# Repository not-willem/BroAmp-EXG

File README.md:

# BroAmp EXG
a decent sized bio amp so i can wire it myself and so that it will be cheaper to produce unlike the other ones on the market 

go to the website i made [here](https://not-willem.github.io/BroAmp-EXG/)

# overview
BroAmp EXG is an open-source project created by yours truly that allows you to turn different body functions that produce a small amount of electricity and amplify them into a more readable signal.

## features 
 - same as the BioAmp EXG Pill just easier to produce using cheap parts
 - can do EEG (activity in parts of the brain), EMG (muscle activity, e.g when you move your hand), ECG (heart rate detection) and EOG (eye blink detection)
 - i think you could probably use it for more but thats all that it was listed for on the original page
 - it can send the data back to pretty much any microcontroller with an analog input (ADC)
 - you can configure the gain, bandpass, filter and electrodes all on the board itself

## documentation 
 - original project: [here](https://github.com/upsidedownlabs/BioAmp-EXG-Pill)
 - date of modifications: June 2026
 - i have made the capacitors and resistors larger to make it easier to hand solder/machine
 - i have changed the board dimensions to 36.5 mm x 48 mm to again, make it easier to hand solder/machine
 - i have kept the same licsense on the hardware (CERN OHL S v2)
 - i have acknowledged the source on the silkscreen
 - the complete source for the modified design is in this github that you're reading this from

## using the project files
To use the project files provided, download them using the green "Code" button at the top of the page, then Download Zip. All the PCB production files are kept in the "production" folder apart from the BOM.csv which is kept in the main folder. 

## production notes
the only thing you should need to do more micro-soldering for is the main chip itself and the electrodes and bandpass filters. these are optional and you will need to micro solder that on but they are for configuration, which, to be fair you could probably also do on the microcontroller itself. The components can simply be hand soldered and they are spaced apart well enough to not short out in case the wires are touching if you've gotten a bigger capacitor/resistor

thanks to the project by [upsidedownlabs](https://github.com/upsidedownlabs/BioAmp-EXG-Pill) because it was super good and cool. 

software demos [here](https://github.com/upsidedownlabs/BioAmp-EXG-Pill#software)

you can find the pcb files in the production folder

and [here](https://github.com/not-willem/BroAmp-EXG/blob/main/BOM%20and%20notes.csv) some notes and a BOM that you can put straight into LCSC to get the parts

but yeah heres some photos

oh hello there

Also some wiring stuff

also theres more ways you can use this [here](https://github.com/upsidedownlabs/BioAmp-EXG-Pill/tree/main/graphics/circuits/v1.0), its the same pins to wire they're not called anything different.

I haven't actually built it YET (i'll update this when i do) but i've 3d printed a prototype so you can see the size of it

*stalagmite for scale

okay i think i need a hot plate for soldering the smd part but i cant get funded for it so i'll find alternative ways to do it

alright you can just use a heat gun awesome

ALSO big news everyone the total cost of parts per board comes in at around $12.17 NZD so hooray!

that's quite cheap compared to the $59.61 NZD for ONE from the actual website (btw you HAVE to buy 2 you can't just get one)

P.S reading it again it seems the kit i'm refering to comes with "Two BioAmp EXG Pill boards, 15 gel electrodes, four 3-pin angled pin headers, four 3-pin straight pin headers, six alligator clips, and two 1.5 mm electrode cables" but still I find it a little silly you can't just buy the boards themselves

Anyway I really hope you like this project and consider supporting me by starring this project and if you think you'd want to change anything you can fork the project then make a pull request

##### This design is released under the CERN Open Hardware Licence Version 2 - Strongly Reciprocal (CERN-OHL-S-2.0).

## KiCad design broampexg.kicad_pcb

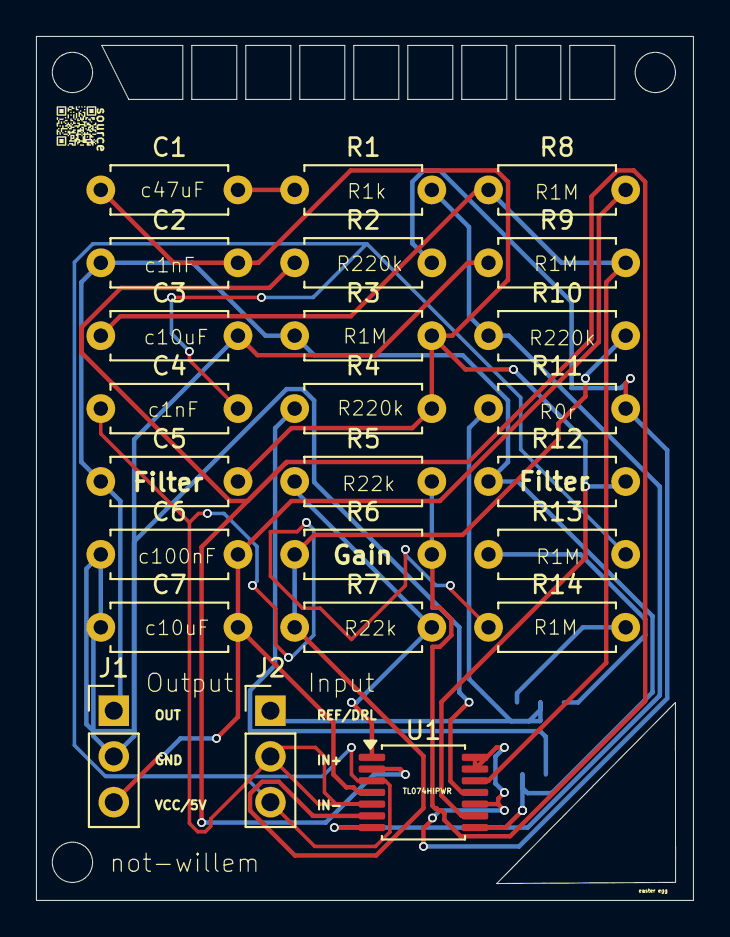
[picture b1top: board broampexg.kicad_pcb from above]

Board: 2 copper layers, 36.5 x 48.0 mm, 24 parts (0 on the bottom side), 14 nets.

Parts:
C1: 47uF; R_Axial_DIN0207_L6.3mm_D2.5mm_P7.62mm_Horizontal
C2, C4: 1nF; R_Axial_DIN0207_L6.3mm_D2.5mm_P7.62mm_Horizontal
C3, C7: 10uF; R_Axial_DIN0207_L6.3mm_D2.5mm_P7.62mm_Horizontal
C5: BPFC_C; R_Axial_DIN0207_L6.3mm_D2.5mm_P7.62mm_Horizontal
C6: 100nF; R_Axial_DIN0207_L6.3mm_D2.5mm_P7.62mm_Horizontal
J1: BioAmp Output; PinHeader_1x03_P2.54mm_Vertical
J2: BioAmp Input; PinHeader_1x03_P2.54mm_Vertical
R1: 1K; R_Axial_DIN0207_L6.3mm_D2.5mm_P7.62mm_Horizontal
R2, R4, R10: 220K; R_Axial_DIN0207_L6.3mm_D2.5mm_P7.62mm_Horizontal
R3, R8, R9, R13, R14: 1M; R_Axial_DIN0207_L6.3mm_D2.5mm_P7.62mm_Horizontal
R5, R7: 22K; R_Axial_DIN0207_L6.3mm_D2.5mm_P7.62mm_Horizontal
R6: RG; R_Axial_DIN0207_L6.3mm_D2.5mm_P7.62mm_Horizontal
R11: 0R; R_Axial_DIN0207_L6.3mm_D2.5mm_P7.62mm_Horizontal
R12: BPFC_R; R_Axial_DIN0207_L6.3mm_D2.5mm_P7.62mm_Horizontal
U1: Amp; TSSOP-14_4.4x5mm_P0.65mm

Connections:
DRL: J2.1, R11.1
GND: C3.2, C6.1, C7.1, J1.2, R9.1, U1.11 (V-)
IN+: C4.1, J2.2, R14.1, U1.5 (+)
IN-: C4.2, J2.3, R13.2, U1.3 (+)
unnamed: C1.2, R1.1
unnamed: R5.1, R7.2, U1.1
unnamed: R2.1, R5.2, R6.2, U1.2 (-)
unnamed: R6.1, R7.1, R10.2, U1.6 (-)
unnamed: C3.1, R8.1, R9.2, U1.12 (+)
VCC: C6.2, C7.2, J1.3, R8.2, U1.4 (V+)
ampRef: R2.2, R11.2, U1.10 (+), U1.13 (-), U1.14
bpfIN: C1.1, C2.2, C5.2, R3.2, R4.2, R12.2, U1.9 (-)
bpfOUT: C2.1, C5.1, J1.1, R3.1, R12.1, U1.8
inaOUT: R1.2, R10.1, U1.7

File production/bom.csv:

Designator,Footprint,Quantity,Value,LCSC Part #
_2,SolderJumper-3_P1.3mm_Open_RoundedPad1.0x1.5mm,1,SolderJumper_3_Open,
,SolderJumper-2_P1.3mm_Open_RoundedPad1.0x1.5mm,1,SolderJumper_2_Open,
C1,R_Axial_DIN0207_L6.3mm_D2.5mm_P7.62mm_Horizontal,1,47uF,
"C2, C4",R_Axial_DIN0207_L6.3mm_D2.5mm_P7.62mm_Horizontal,2,1nF,
"C3, C7",R_Axial_DIN0207_L6.3mm_D2.5mm_P7.62mm_Horizontal,2,10uF,
C5,R_Axial_DIN0207_L6.3mm_D2.5mm_P7.62mm_Horizontal,1,BPFC_C,
C6,R_Axial_DIN0207_L6.3mm_D2.5mm_P7.62mm_Horizontal,1,100nF,
J1,PinHeader_1x03_P2.54mm_Vertical,1,BioAmp Output,
J2,PinHeader_1x03_P2.54mm_Vertical,1,BioAmp Input,
R1,R_Axial_DIN0207_L6.3mm_D2.5mm_P7.62mm_Horizontal,1,1K,
"R10, R2, R4",R_Axial_DIN0207_L6.3mm_D2.5mm_P7.62mm_Horizontal,3,220K,
R11,R_Axial_DIN0207_L6.3mm_D2.5mm_P7.62mm_Horizontal,1,0R,
R12,R_Axial_DIN0207_L6.3mm_D2.5mm_P7.62mm_Horizontal,1,BPFC_R,
"R13, R14, R3, R8, R9",R_Axial_DIN0207_L6.3mm_D2.5mm_P7.62mm_Horizontal,5,1M,
"R5, R7",R_Axial_DIN0207_L6.3mm_D2.5mm_P7.62mm_Horizontal,2,22K,
R6,R_Axial_DIN0207_L6.3mm_D2.5mm_P7.62mm_Horizontal,1,RG,
U1,TSSOP-14_4.4x5mm_P0.65mm,1,Amp,

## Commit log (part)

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2026-06-30 added in all the files yay
    free
2026-06-30 dadgagdagd
    dgadgagda
2026-06-30 imaegs
2026-06-30 dgdggdagdadga
    gad
2026-06-30 fonts and stuff yay
